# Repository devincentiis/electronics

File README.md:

# My electronic projects shared with every enthusiasts.
## Used KiCAD EDA for design schematic diagrams and PCB 

### [Classic ESR meter](https://github.com/devincentiis/electronics/blob/main/AntonioDeVincentiis_classicESRmeter) 
 Open-Source In-Circuit ESR Meter (ATtiny412)

### [PRESSFLOWino](https://github.com/devincentiis/electronics/blob/main/PRESSFLOWino) 
Multimode, customizable press and flow controller with ATmega328P

### [Water Flush Muse](https://github.com/devincentiis/electronics/blob/main/WaterFlushMuse) 
ATtiny412 water waste tank alarm

## License

MIT License

Copyright (c) 2023 to present - Antonio de Vincentiis

Permission is hereby granted, free of charge, to any person obtaining a copy
of this software and associated documentation files (the "Software"), to deal
in the Software without restriction, including without limitation the rights
to use, copy, modify, merge, publish, distribute, sublicense, and/or sell
copies of the Software, and to permit persons to whom the Software is
furnished to do so, subject to the following conditions:

The above copyright notice and this permission notice shall be included in all
copies or substantial portions of the Software.

THE SOFTWARE IS PROVIDED "AS IS", WITHOUT WARRANTY OF ANY KIND, EXPRESS OR
IMPLIED, INCLUDING BUT NOT LIMITED TO THE WARRANTIES OF MERCHANTABILITY,
FITNESS FOR A PARTICULAR PURPOSE AND NONINFRINGEMENT. IN NO EVENT SHALL THE
AUTHORS OR COPYRIGHT HOLDERS BE LIABLE FOR ANY CLAIM, DAMAGES OR OTHER
LIABILITY, WHETHER IN AN ACTION OF CONTRACT, TORT OR OTHERWISE, ARISING FROM,
OUT OF OR IN CONNECTION WITH THE SOFTWARE OR THE USE OR OTHER DEALINGS IN THE
SOFTWARE.

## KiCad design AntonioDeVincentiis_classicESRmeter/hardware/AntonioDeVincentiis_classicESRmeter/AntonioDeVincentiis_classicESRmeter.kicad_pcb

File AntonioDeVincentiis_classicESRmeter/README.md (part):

# 🛠️ Classic ESR meter
In-Circuit ESR Meter standalone ATtiny412 platform.

---

## 🌍 Language / Lingua
Select your preferred language:
* 🇬🇧 [English Version](#-english-version)
* 🇮🇹 [Versione Italiana](#-versione-italiana)

---

*ESRmeter 85C1 100uA - Case Model T*
## 🇬🇧 English Version

### The innovation:💡
What distinguishes this from the many other circuit solutions found online is the inclusion of a 10 Ω resistor in parallel with the electrolytic capacitor under test. While this prevents ESR measurements beyond a few tens of ohms (which are of no practical use), it offers significant advantages: it creates a resistive voltage divider that eliminates the need for constant-current generators, limits the maximum voltage across the component, allows the capacitor to discharge as quickly as it charges, and provides better protection than the standard pair of anti-parallel diodes.

A complete project [Hardware](./hardware/AntonioDeVincentiis_classicESRmeter/), [Firmware](./firmware/AntonioDeVincentiis_classicESRmeter/), and [Case 3D files](./case/) to build a **high-precision analog ESR Meter** optimized for direct *in-circuit* measurements (without desoldering capacitors). The instrument can resolve variations down to **0.01 Ω** in the critical zone of the scale, extending its logarithmic readout up to **20 Ω**.

The software architecture is developed in C++ for the **ATtiny412** using the Arduino IDE (via the `megaTinyCore` library). It performs deterministic sampling at 100 kHz without requiring external Sample & Hold components, using only signal conditioning/amplification through two common BC850C low-noise transistors.

### 🚀 Key Features
* **Realistic In-Circuit Measurement:** Operates at a low excitation voltage to prevent surrounding semiconductor junctions from turning on during in-circuit testing.
* **Synchronous S&H Sampling (Anti-ESL):** Utilizes the hardware **Event System** integrated into AVR 1-series MCUs to synchronize ADC0 with the 100 kHz square wave timer. By sampling exactly ~3 µs after the cycle start, the instrument isolates the ESR, eliminating parasitic inductive reactance (ESL) spikes.
* **Oversampling and Advanced Filtering:** Executes 64x hardware oversampling combined with a software **EMA (Exponential Moving Average)** filter to guarantee a perfectly stable, vibration-free meter needle.
* **Fixed-Point Logarithmic Scale:** Fast polynomial approximation maps ESR values onto the analog microammeter, ensuring extremely high sub-ohm resolution while expanding readability up to 20 Ω.
* **Smart Power Management (Kill-Switch):** Total shutdown via a Latch MOSFET paired with an auto-power-off feature ensures ~0 mA parasitic current draw in standby.

### ⏳ History

This project was born to solve a well-known issue in electronics troubleshooting: making precise, in-circuit ESR measurements without desoldering components. The initial goal was ambitious yet budget-friendly: creating a tool capable of 0.01 Ω sensitivity without relying on expensive and complex microcontrollers.

The development took a few months and progressed through these key milestones:

* **1. Genesis & Simulation:** The initial concept featured fast operational amplifiers and a precision rectifier. SPICE simulations validated the theory, producing millivolt outputs perfectly readable by a 10-bit ADC (ranging from 0.2 mV for 0.01 Ω up to over 400 mV for 20 Ω).
* **2. The Inductance (ESL) Challenge:** Deeper simulation revealed that inductive reactance caused unwanted voltage spikes on the edges of the 100 kHz square wave. This was solved by replacing the standard rectifier with a delayed *Sample & Hold* approach, bypassing the first 3 µs of spikes to sample only the clean plateau.
* **3. Hardware Simplification & Thermal Compensation:** To lower production costs, the external S&H circuit was replaced by utilizing the MCU's internal ADC, conditioning the signal with just two common BJT transistors. To prevent thermal drift from affecting low-range readings, a compensation diode was added. The firmware checks this at boot, warning the user via a sweeping meter needle if the offset shifts outside the 0.95V - 1.05V tolerance.
* **4. Lab Testing & Real-World Validation:** Once the definitive PCBs arrived, real-world tests exceeded expectations. Pairing the board with custom-made, low-cost Kelvin probes allowed the ADC to resolve variations down to 3.33 mΩ.
* **5. Firmware & Dual-Scale Optimization:** The final challenge was fitting the software into an ultra-cheap 50-cent MCU (ATtiny412). By heavily optimizing timers and ADC registers to sample within 1-2 µs, the firmware takes up just 80% of the memory. It implements an intelligent dual-scale system: Scale 1 (0.01 Ω to 1.00 Ω) for maximum precision, and Scale 2 (1 Ω to 20 Ω) for general readings.

### 📐 Pinout & Connections (ATtiny412)

| Pin | Name | Type | Main Function |
| :---: | :---: | :---: | :--- |
| **1** | VDD | Power | +5V Power Supply |
| **2** | PA6 | Output | ~610 Hz Analog PWM Output (Microammeter Control) |
| **3** | PA7 | Input | ADC0 Analog Input / AIN7 Channel (ESR Sensor) |
| **4** | PA1 | Output | 100 kHz Hardware Square Wave Generation (TCA0) |
| **5** | PA2 | Input | Multi-function Button Input (On/Off/Calibration) / Serial in MODE 1 |
| **6** | PA0 | I/O | UPDI Programming Line |
| **7** | PA3 | Output | Latch MOSFET Control (Power Hold) |
| **8** | GND | Power | Common Circuit Ground |

### 🔧 Configuration and Calibration Guide (FIRMWARE_USAGE_MODE)
The firmware implements a guided calibration sequence managed via the `#define FIRMWARE_USAGE_MODE` macro at the top of the sketch:

#### 🟩 Step 1: MODE 0 - Static Hardware Calibration
Set the macro to `0` and upload the firmware. The 100 kHz carrier is deactivated, and the PWM output to the analog meter is forced to its maximum value (`1023`).
1. Rotate the hardware trimmer **RV2** until you measure exactly **1.000 V** at the `SIGNAL_TO_ADC` test point (BJT sensor bias voltage).
2. Adjust trimmer **RV1** to force the needle of your analog microammeter (e.g., 100µA or 1mA) precisely to the full-scale **0 Ω** mark.

<details>
  <summary>💾 <ins>Click here to view the firmware MODE 0(.hex)</ins></summary>
  <br>

```hex
:1000000019C03FC03EC03DC03CC03BC03AC039C033
:1000100038C037C036C035C034C033C033C031C03B
:1000200030C05FC02EC02DC02CC02BC02AC029C03C
:1000300028C027C011241FBECFEFCDBFDFE3DEBF36
:100040008091400080934000811105C098ED21E02F
:1000500094BF209341008CBB1FE3A0E0BFE3E8EC1A
:10006000F3E002C005900D92A630B107D9F72FE357
:10007000A6E0BFE301C01D92AC31B207E1F76FD03B
:10008000A1C1BECF8F9381E080938D0A8FB78F93EC
:10009000EF93FF93E2E1FFE39F9368948FEF0DC02E
:1000A000E89484819581805D9C4F84839583885EEC
:1000B000934080F0848395838FEF9081981B919378
:1000C00090819F4F919390819F4F919390819F4FEB
:1000D000919336F39F91FF91EF918F918FBF8F9105
:1000E00018951F920F920FB60F9211242F933F93E2
:1000F0008F939F93AF93BF93209110063091110679
:1001000080910D3F811120C08091093F90910A3F5D
:10011000A0910B3FB0910C3F820F931FA11DB11D09
:100120008093093F90930A3FA0930B3FB0930C3FFD
:100130008091063F8F5F8093063F8091063F803419
:100140001CF081E080930D3FBF91AF919F918F9103
:100150003F912F910F900FBE0F901F90189588ED33
:1001600090E084BF90936100E0E0F6E083E5828355
:100170008DE0858380E2838381E080838093020227
:100180008093030A9EEF9093260A9093270A9BE0A0
:100190009093000AE0E8FAE02DEF31E026A737A7B8
:1001A000118290E89283848781E1808378948091A2
:1001B00000148093013F809101148093023F80914D
:1001C000013F9091023F845F9140893C910530F05E
:1001D00088E592E08093013F9093023FF89410925B
:1001E000000A8091003F8F7E8093003F8FE08093D4
:1001F000050A88E0809301048093050480E48093DD
:10020000010480E88093020484E08093170492E064
:100210009093020420E12093A0009093A10081E03C
:100220008093000610920106909302061092030636
:1002300097E0909306068093090680930A06109231
:10024000800A8FEF93E08093AE0A9093AF0A1092EA
:10025000A80A1092A90A1092AA0A1092AB0A88ED75
:1002600084BF2093920A80918E0A81FFFCCF81E7A0
:100270008093800A1092000A8CE08093050A109205
:10028000030A87EC90E08093260A9093270A8CE873
:1002900090E08093280A9093290A84E690E0809366
:1002A0002A0A90932B0A83E08093010A809102022C
:1002B00081608093020210920A0A84E680938A0188
:1002C00081E08093930180930B068093000A7894D9
:1002D0004FEF53E062E02FB7F8948091163F909172
:1002E000173FA091183FB091193F2FBF00910E3FCB
:1002F00010910F3F2091103F3091113F801B910BC7
:10030000A20BB30B84369105A105B10520F32FB7DD
:10031000F8948091163F9091173FA091183FB091AB
:10032000193F2FBF80930E3F90930F3FA093103F34
:10033000B093113F80910D3F882369F28091093F6E
:1003400090910A3FA0910B3FB0910C3FF6E0B5951C
:10035000A79597958795FA95D1F78093073F909346
:10036000083FF8942091033F3091043F8091073F6C
:100370009091083F37FF1CC0880F991F880F991F65
:100380008093033F9093043F4093AA0A5093AB0A93
:100390006093840A1092093F10920A3F10920B3F1B
:1003A00010920C3F1092063F10920D3F789493CF1D
:1003B000F901F595E795F595E7958E1B9F0B820F53
:0803C000931FDECFF894FFCF7C
:0603C800FF5802FFFF00D8
:00000001FF
```

</details>

#### 🟦 Step 2: MODE 1 - Debug and Constant Acquisition
Set the macro to `1` and upload the firmware. This mode activates the 100 kHz signal and enables a software serial port on pin `PA2` at 9600 baud.
1. Connect a USB-TTL converter (Converter Rx to MCU pin PA2).
2. Open the Serial Monitor and note the `ADC_RAW` value with shorted probes (`ADC_ZERO`, typically ~945) and open probes (`ADC_OPEN`, typically ~130).
3. If your real-world values differ from the default ones, update the definitions at the top of the sketch before the final flash.

<details>
  <summary>💾 <ins>Click here to view the firmware MODE 1(.hex)</ins></summary>
  <br>

```hex
:100000001BC04BC04AC01CC248C047C046C045C008
:1000100044C043C042C041C040C03FC0E2C13DC037
:100020003CC058C23AC039C038C037C036C035C0ED
:1000300034C033C02405960511241FBECFEFCDBFB9
:10004000DFE3DEBF8091400080934000811105C056
:1000500098ED21E094BF209341008CBB1FE3A0E00A
:10006000BFE3E2EFFCE002C005900D92A830B107BB
:10007000D9F72FE3A8E0BFE301C01D92AD38B20766
:10008000E1F710E0CBE1D0E003C02197FE01DBD522
:10009000CA31D107D1F75CD2E8C5B2CFE0915A3F5F
:1000A000F0915B3F309709F44DC0A285B3858185FF
:1000B000928D91FF04C09C91892329F408959C910D
:1000C000892309F03FC0A785B0899C9181898095DB
:1000D00089238C93828993890197F1F764897589C3
:1000E000A285B385518538E020E0CB010197F1F777
:1000F000822F90E095958795282F4C91452309F004
:100100002068315091F7828D81FD20958091593F73
:1001100090E001968F7399273091583F381799F0E6
:10012000A091593FB0E0A85EB04C2C938093593F0A
:10013000868997890197F1F7A785B0898C91918974
:10014000892B8C930895828D8160828FF1CFAF923D
:10015000BF92CF92DF92EF92FF920F931F93CF93B4
:10016000DF936C017B018B01040F151FEB015E0116
:10017000AE18BF08C017D10759F06991D601ED91AB
:10018000FC910190F081E02DC6010995892B79F74A
:10019000C501DF91CF911F910F91FF90EF90DF90FC
:1001A000CF90BF90AF90089520915A3F30915B3F20
:1001B0002817390771F49091583F8091593F98174B
:1001C00041F0E091583FF0E0E85EF04C808190E033
:1001D00008958FEF9FEF08950895EF92FF920F9388
:1001E0001F93CF93DF93DC015896ED90FC905997C5
:1001F000E114F10479F481E090E012968D939C93E0
:10020000139790E080E0DF91CF911F910F91FF90C5
:10021000EF9008951D96ED91FC911E971C968C9180
:100220001C97982F90950FB75A962C915A97122F8A
:10023000127021FD6095F8942081112319F1282B6B
:100240002083E7012197F1F728E0462F50E0308125
:1002500060FF1AC0382B3083E7012197F1F7BA010C
:1002600075956795215089F7112381F08081892345
:1002700080830FBF58968D919C910197F1F781E093
:1002800090E0C1CF2923DCCF3923E5CF9081892BA2
:10029000EFCF20915A3F30915B3F2817390741F447
:1002A0008091593F9091583F891B8F7390E008953A
:1002B00090E080E0089520915A3F30915B3F2817ED
:1002C0003907A1F49091583F8091593F981771F0E8
:1002D000E091583FF0E0E85EF04C80819091583F0B
:1002E0009F5F9F739093583F90E008958FEF9FEF2B
:1002F000089590E080E00895FC0101900020E9F766
:100300003197AF01481B590BBC0182E79FE31FCF18
:100310008F929F92AF92BF920F931F93CF93DF93D1
:10032000CDB7DEB7A197CDBFDEBF19A2423008F42A
:100330004AE08E010F5D1F4F842E912CB12CA12C11
:10034000A501940132D4E62FB901CA01EA30D4F4F0
:10035000E05DD801EE938D01232B242B252B81F713
:1003600090E080E0109711F0CD01C6DFA196CDBFDF
:10037000DEBFDF91CF911F910F91BF90AF909F9003
:100380008F900895E95CE5CFCF92DF92EF92FF92D4
:10039000CF93DF936C01990FEE08FF08F7FE17C0AB
:1003A0006DE282E79FE319DFEC0166277727CB0137
:1003B0006C197D098E099F094AE0AADF8C0F9D1FE9
:1003C000DF91CF91FF90EF90DF90CF9008954AE0BA
:1003D000C701B601DF91CF91FF90EF90DF90CF90F2
:1003E00097CF8F9381E080938D0A8FB78F93EF9390
:1003F000FF93E8E6FFE39F9368948FEF0DC0E894C6
:1004000084819581805D9C4F84839583885E934031
:1004100080F0848395838FEF9081981B91939081D6
:100420009F4F919390819F4F919390819F4F919374
:1004300036F39F91FF91EF918F918FBF8F91189518
:100440000F9300E000C00F920FB60F921F9211247D
:10045000FF921F932F933F934F935F936F937F93DD
:100460008F939F93AF93BF93CF93DF93EF93FF93BC
:10047000A1E0BFE3A00FB11DCD91DC91000F0D5F96
:10048000A02FB0E0FC90109761F01F2D169518F08A
:1004900041F02296FBCFE991F9913097B9F3099594
:1004A000F5CFA02FB0E0FC92FF91EF91DF91CF91BB
:1004B000BF91AF919F918F917F916F915F914F917C
:1004C0003F912F911F91FF901F900F900FBE0F90A3
:1004D0000F9118951F920F920FB60F9211242F9320
:1004E0003F938F939F93AF93BF93209110063091CA
:1004F00011068091633F811120C080915F3F9091F0
:10050000603FA091613FB091623F820F931FA11D98
:10051000B11D80935F3F9093603FA093613FB09384
:10052000623F80915C3F8F5F80935C3F80915C3F36
:1005300080341CF081E08093633FBF91AF919F9125
:100540008F913F912F910F900FBE0F901F90189594
:1005500088ED90E084BF90936100E0E0F6E083E5F1
:1005600082838DE0858380E2838381E08083809332
:1005700002028093030A9EEF9093260A9093270A23
:100580009BE09093000AE0E8FAE02DEF31E026A727
:1005900037A7118290E89283848781E180837894E1
:1005A000809100148093033F809101148093043F55
:1005B0008091033F9091043F845F9140893C910575
:1005C00030F088E592E08093033F9093043FF894E5
:1005D0001092000A8091003F8F7E8093003F8FE051
:1005E0008093050A88E0809301048093050480E4E9
:1005F0008093010480E88093020484E080931704D0
:1006000092E09093010420E12093A0009093A10038
:1006100081E08093000610920106909302061092EA
:10062000030697E0909306068093090680930A06D6
:100630001092800A8FEF93E08093AE0A9093AF0AF6
:100640001092A80A1092A90A1092AA0A1092AB0A54
:1006500088ED84BF2093920A80918E0A81FFFCCF9F
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
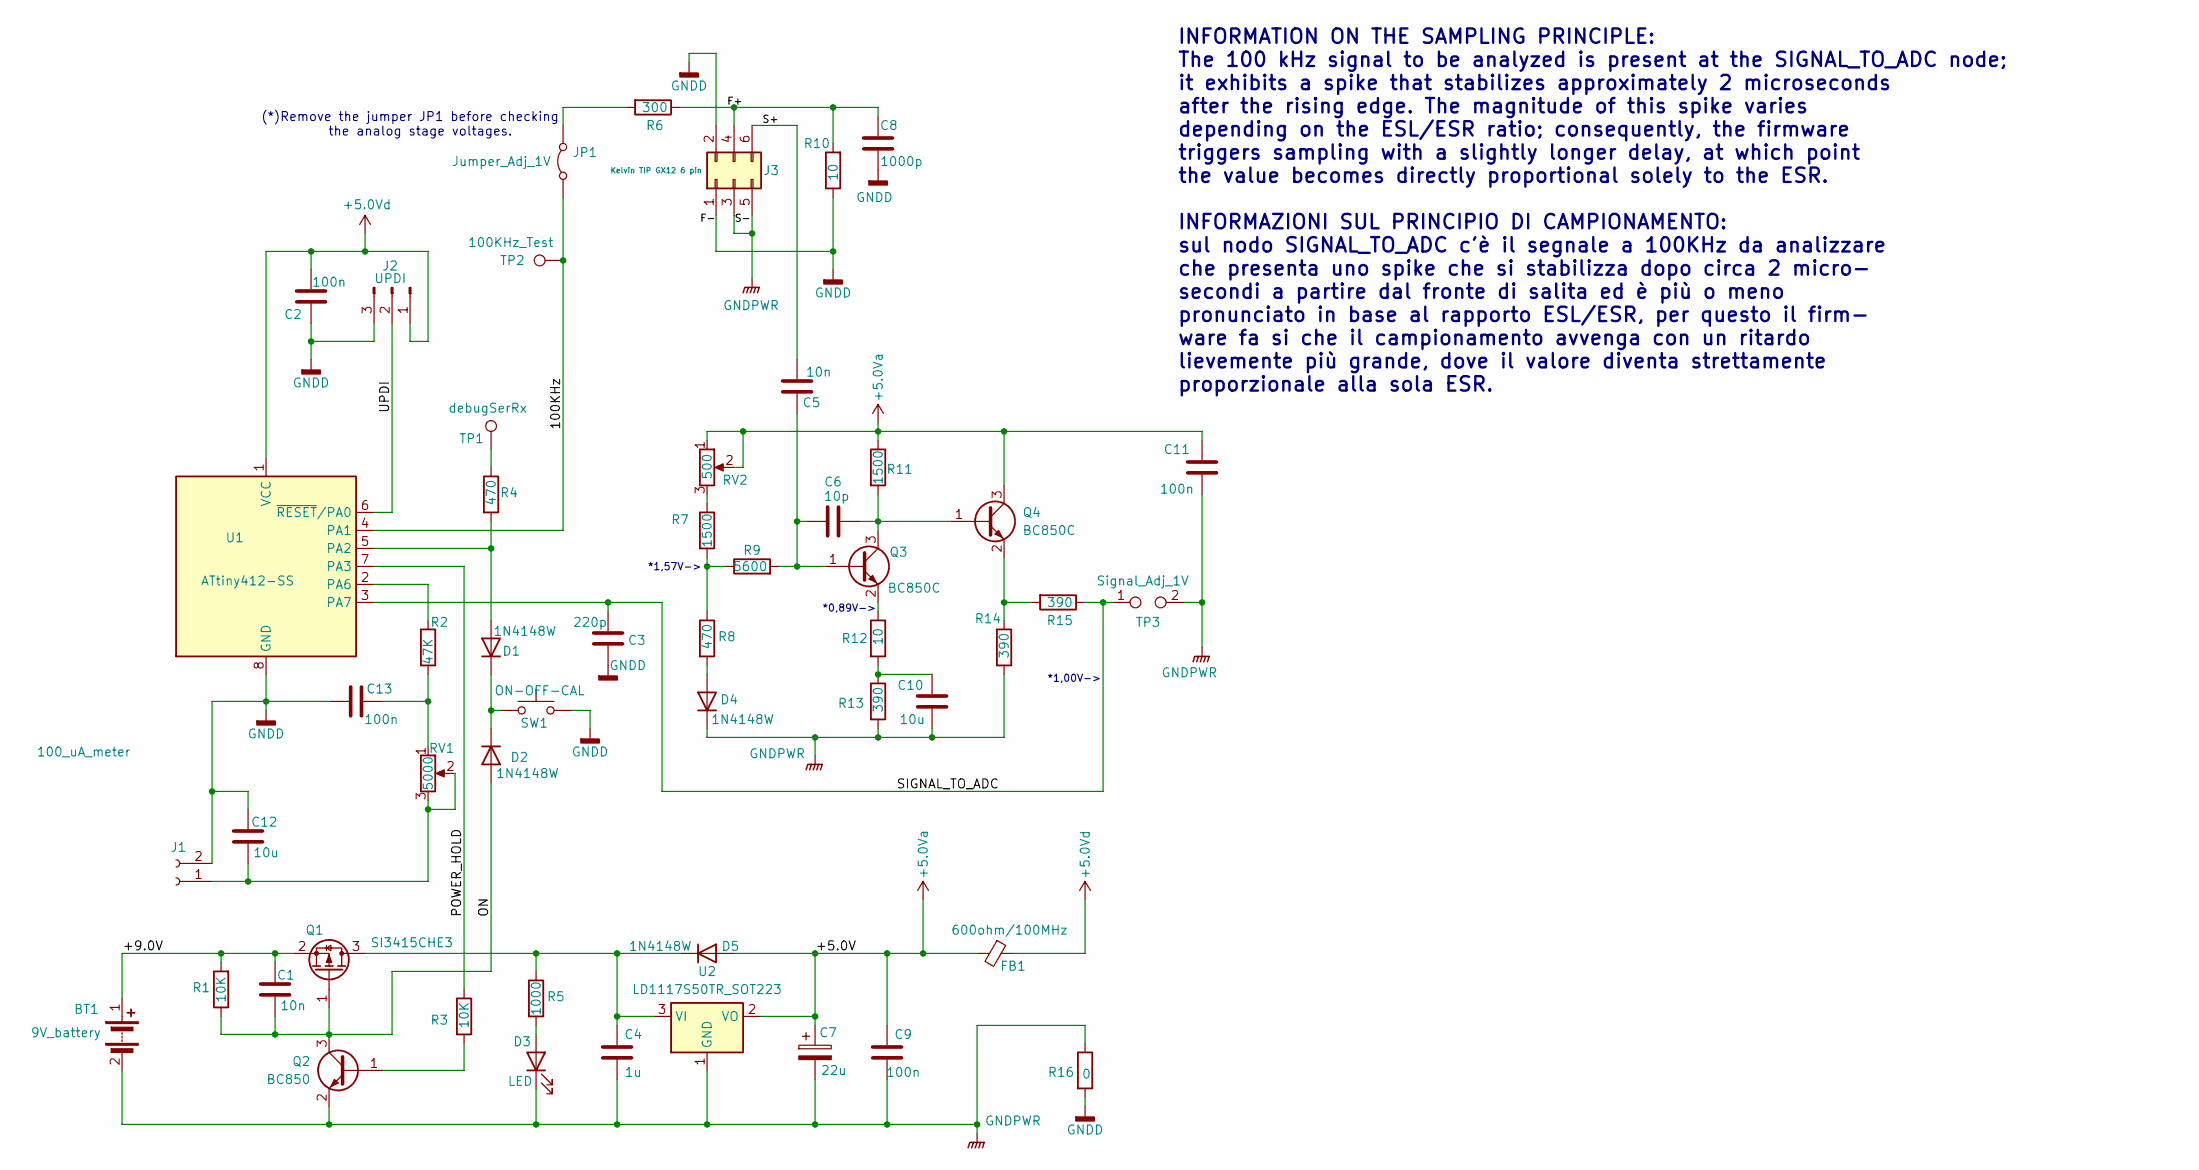
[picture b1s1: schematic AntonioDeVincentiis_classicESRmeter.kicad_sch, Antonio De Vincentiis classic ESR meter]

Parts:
BT1: 9V_battery; PinSocket_1x02_P2.54mm_Vertical
C1, C5: 10n; C_0805_2012Metric_Pad1.18x1.45mm_HandSolder
C2, C9, C11, C13: 100n; C_0805_2012Metric_Pad1.18x1.45mm_HandSolder
C3: 220p; C_0805_2012Metric_Pad1.18x1.45mm_HandSolder
C4: 1u; C_0805_2012Metric_Pad1.18x1.45mm_HandSolder
C6: 10p; C_0805_2012Metric_Pad1.18x1.45mm_HandSolder
C7: 22u; CP_Elec_5x5.9
C8: 1000p; C_0805_2012Metric_Pad1.18x1.45mm_HandSolder
C10, C12: 10u; C_0805_2012Metric_Pad1.18x1.45mm_HandSolder
D1, D2, D4, D5: 1N4148W; D_SOD-123
D3: LED; LED_D3.0mm_Clear
FB1: 600ohm/100MHz; L_0805_2012Metric_Pad1.05x1.20mm_HandSolder
J1: 100_uA_meter; PinSocket_1x02_P2.54mm_Vertical
J2: UPDI; PinSocket_1x03_P2.54mm_Vertical
J3: Kelvin TIP GX12 6 pin; PinSocket_2x03_P2.54mm_Vertical
JP1: Jumper_Adj_1V; PinHeader_2x01_P2.54mm_Vertical
Q1: SI3415CHE3; SOT-23_Handsoldering
Q2: BC850; SOT-23
Q3, Q4: BC850C; SOT-23
R1, R3: 10K; R_0805_2012Metric_Pad1.20x1.40mm_HandSolder
R2: 47K; R_0805_2012Metric_Pad1.20x1.40mm_HandSolder
R4, R8: 470; R_0805_2012Metric_Pad1.20x1.40mm_HandSolder
R5: 1000; R_0805_2012Metric_Pad1.20x1.40mm_HandSolder
R6: 300; R_0805_2012Metric_Pad1.20x1.40mm_HandSolder
R7, R11: 1500; R_0805_2012Metric_Pad1.20x1.40mm_HandSolder
R9: 5600; R_0805_2012Metric_Pad1.20x1.40mm_HandSolder
R10: 10; R_2010_5025Metric_Pad1.40x2.65mm_HandSolder
R12: 10; R_0805_2012Metric_Pad1.20x1.40mm_HandSolder
R13, R14, R15: 390; R_0805_2012Metric_Pad1.20x1.40mm_HandSolder
R16: 0; R_0805_2012Metric_Pad1.20x1.40mm_HandSolder
RV1: 5000; Potentiometer_Bourns_3296W_Vertical
RV2: 500; Potentiometer_Bourns_3296W_Vertical
SW1: ON-OFF-CAL; SW_PUSH_6mm_H5mm
TP1: debugSerRx; PinSocket_1x01_P2.54mm_Vertical
TP2: 100KHz_Test; PinSocket_1x01_P2.54mm_Vertical
TP3: Signal_Adj_1V; PinSocket_1x02_P2.54mm_Vertical
U1: ATtiny412-SS; SOIC-8_3.9x4.9mm_P1.27mm
U2: LD1117S50TR_SOT223; SOT-223-3_TabPin2

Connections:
+5.0Va: C7.1, C9.1, C11.1, D5.2 (A), FB1.2, Q4.3 (C), R11.1, RV2.1, RV2.2, U2.2 (VO)
+5.0Vd: C2.1, FB1.1, J2.1, U1.1 (VCC)
/100KHz: JP1.1 (A), TP2.1 (1_1), U1.4 (PA1)
/+9.0V: BT1.1 (+4.5V), C1.1, Q1.2 (S), R1.2
/F+: C8.1, J3.4, R6.1, R10.2
/ON: C1.2, D2.2 (A), Q1.1 (G), Q2.3 (C), R1.1
/POWER_HOLD: R3.1, U1.7 (PA3)
/S+: C5.1, J3.6
/SIGNAL_TO_ADC: C3.1, R15.1, TP3.1, U1.3 (PA7)
/UPDI: J2.2, U1.6 (~RESET/PA0)
GNDD: C2.2, C3.2, C8.2, C12.1, C13.1, J1.2, J2.3, J3.1, J3.2, R10.1, R16.2, SW1.2, U1.8 (GND)
GNDPWR: BT1.2 (-), C4.2, C7.2, C9.2, C10.2, C11.2, D3.1 (K), D4.1 (K), J3.3, J3.5, Q2.2 (E), R13.2, R14.2, R16.1, TP3.2, U2.1 (GND)
unnamed: C10.1, R12.2, R13.1
unnamed: C13.2, R2.2, RV1.1
unnamed: D1.2 (A), R4.2, U1.5 (PA2)
unnamed: D1.1 (K), D2.1 (K), SW1.1
unnamed: D3.2 (A), R5.2
unnamed: D4.2 (A), R8.2
unnamed: C4.1, D5.1 (K), Q1.3 (D), R5.1, U2.3 (VI)
unnamed: C12.2, J1.1, RV1.2, RV1.3
unnamed: JP1.2 (B), R6.2
unnamed: Q2.1 (B), R3.2
unnamed: C5.2, C6.1, Q3.1 (B), R9.2
unnamed: C6.2, Q3.3 (C), Q4.1 (B), R11.2
unnamed: Q3.2 (E), R12.1
unnamed: Q4.2 (E), R14.1, R15.2
unnamed: R4.1, TP1.1 (1_1)
unnamed: R7.1, RV2.3
unnamed: R7.2, R8.1, R9.1
unnamed: R2.1, U1.2 (PA6)

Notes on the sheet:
*1,00V->
*0,89V->
*1,57V->
INFORMATION ON THE SAMPLING PRINCIPLE: The 100 kHz signal to be analyzed is present at the SIGNAL_TO_ADC node; it exhibits a spike that stabilizes approximately 2 microseconds after the rising edge. The magnitude of this spike varies depending on the ESL/ESR ratio; consequently, the firmware trigge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
(*)Remove the jumper JP1 before checking the analog stage voltages.

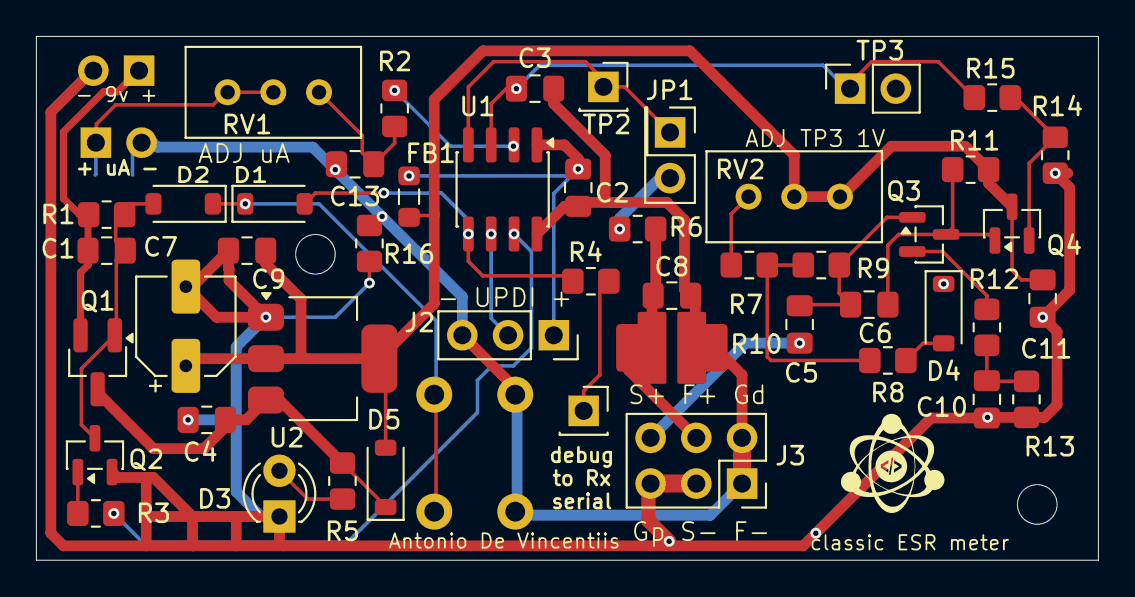
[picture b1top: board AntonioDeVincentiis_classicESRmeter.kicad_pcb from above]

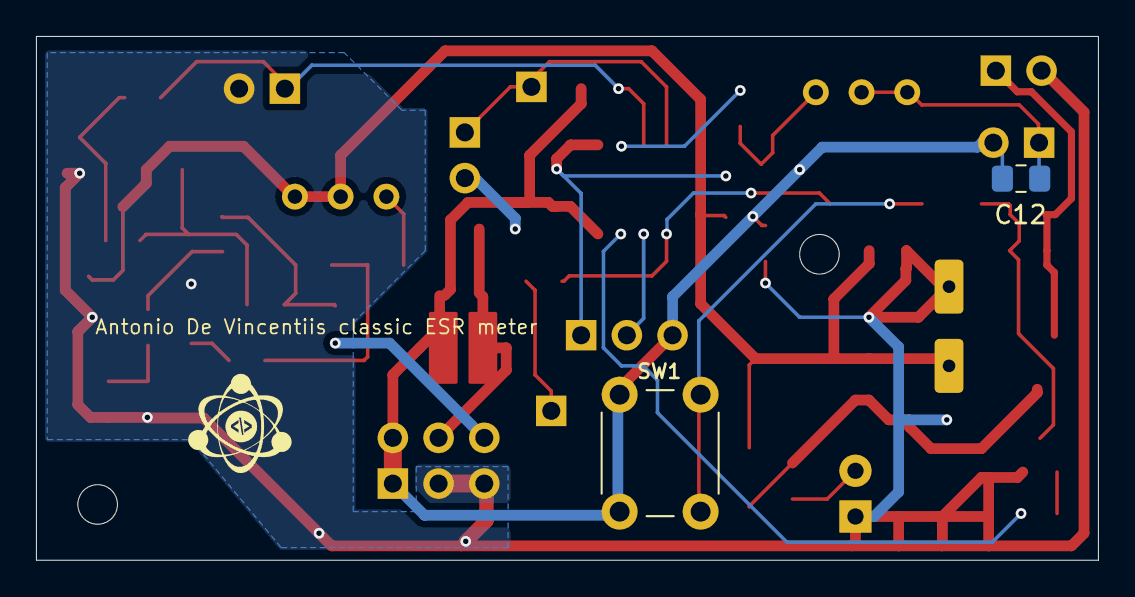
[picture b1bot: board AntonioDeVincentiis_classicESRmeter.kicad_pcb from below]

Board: 2 copper layers, 59.0 x 29.1 mm, 52 parts (2 on the bottom side), 30 nets.

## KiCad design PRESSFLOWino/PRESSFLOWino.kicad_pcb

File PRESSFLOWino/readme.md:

# PRESSFLOWino - Multimode, customizable press and flow controller
## for air compressor, water pump and other device

Base on Atmel ATmega328P 32 pins and compiled trought Arduino IDE and ADVcapacitiveSensor library. The circuit is shared for the purpose of making you participate in the improvement of the [FIRMWARE](https://github.com/devincentiis/electronics/blob/main/PRESSFLOWino/firmwarePressFlow/firmwarePressFlow.ino); for safety reasons and $\textsf{\color{orange}{to avoid risks of electric shock it is essential to power it at 48 Vac}}$ for the Triacs and at 5 Vdc for the digital section. Therefore, **anyone attempting to implement it in practice must be qualified and assumes all civil and criminal liability.**

**DECLARATION OF RESPONSIBILITY**

**The author therefore assumes NO RESPONSIBILITY** in civil or criminal matters and does not offer any implicit or explicit guarantee, and is not responsible for problems of any kind, damages or accidents deriving from the use of the information found on this web page , as well as from the use of the page itself or part of it. **Anyone who creates and/or uses modifications, diagrams, electrical circuits**, or mechanical parts or electronic theory information described here, **does so as their own free choice, assuming all responsibilities that may derive from them**, and will therefore not be able to claim any form of compensation from the author, in case of damage or accidents for everything described and said. In light of the above and **in consideration of the danger of electrocution deriving from the connection with voltages highter than 48V ac**, the description on this project has been deliberately omitted and **remains the responsibility of qualified personnel in the electrical/electronic sector**.

### Use instructions
By touch the 4 buttons (ENTER, UP, DOWN, BACK) you can select the parameters for the target device of the control.
* Select the type of device to control: pump or compressor.
* Select the pressure sensor or customize it.
* Select flow sensor as switch, none, preset or customize it.

### Schematic and PCB EDA [KiCad](https://www.kicad.org/download/) 

### Firmware library for [Arduino IDE](https://github.com/arduino/Arduino) 

| Reference        | Value        | Footprint                                                      | Qty |
|------------------|--------------|----------------------------------------------------------------|-----|
| BZ1              | Buzzer       | Buzzer_Beeper:Buzzer_12x9.5RM7.6                               | 1   |
| C1,C6,C7,C10,C13 | 100n         | Capacitor_SMD:C_1206_3216Metric_Pad1.33x1.80mm_HandSolder      | 5   |
| C2,C4            | 100n 400V    | Capacitor_THT:C_Rect_L19.0mm_W6.0mm_P15.00mm_MKS4              | 2   |
| C3               | 10n 400V     | Capacitor_THT:C_Rect_L13.0mm_W5.0mm_P10.00mm_FKS3_FKP3_MKS4    | 1   |
| C5               | 470u         | Capacitor_THT:CP_Radial_D12.5mm_P5.00mm                        | 1   |
| C8               | 10u          | Capacitor_THT:CP_Radial_D5.0mm_P2.50mm                         | 1   |
| C9               | 10nF         | Capacitor_THT:C_Rect_L13.0mm_W5.0mm_P10.00mm_FKS3_FKP3_MKS4    | 1   |
| D1               | LED-ORANGE   | LED_SMD:LED_1206_3216Metric_Pad1.42x1.75mm_HandSolder          | 1   |
| D2,D7            | BT137-600    | Package_TO_SOT_THT:TO-220-3_Vertical                           | 2   |
| D4               | LED-GREEN    | LED_SMD:LED_1206_3216Metric_Pad1.42x1.75mm_HandSolder          | 1   |
| D5,D8            | M4-1N4004    | Diode_SMD:D_SMA                                                | 2   |
| DS1              | 16x02        | Display:WC1602A                                                | 1   |
| F1               | FUSE         | Fuse_THT:Rect_L7.2mm_W4.5mm_P5.00mm                            | 1   |
| H1               | BCK          | MountingHole:MountingHole_3.2mm_M3_Pad_TopBottom               | 1   |
| H2               | ENT          | MountingHole:MountingHole_3.2mm_M3_Pad_TopBottom               | 1   |
| H3               | UP           | MountingHole:MountingHole_3.2mm_M3_Pad_TopBottom               | 1   |
| H4               | DWN          | MountingHole:MountingHole_3.2mm_M3_Pad_TopBottom               | 1   |
| IC1,IC2          | TLP266J      | Package_SO:SO-4_4.4x4.3mm_P2.54mm                              | 2   |
| J1               | ICSP         | Connector_PinHeader_2.54mm:PinHeader_2x03_P2.54mm_Vertical     | 1   |
| J2               | FTDI         | Connector_PinSocket_2.54mm:PinSocket_1x06_P2.54mm_Vertical     | 1   |
| P1               | E_VALVE      | ADVlibrary:Faston6.35-2x7.62                                   | 1   |
| P2               | V ac         | ADVlibrary:Faston6.35-2x7.62                                   | 1   |
| P3               | MOTOR        | ADVlibrary:Faston6.35-2x7.62                                   | 1   |
| P4               | GROUND       | ADVlibrary:Faston6.35-2x7.62                                   | 1   |
| R1,R2,R3,R4      | 4.7M         | Resistor_SMD:R_1206_3216Metric_Pad1.30x1.75mm_HandSolder       | 4   |
| R5,R6,R7,R8,R19  | 1000         | Resistor_SMD:R_1206_3216Metric_Pad1.30x1.75mm_HandSolder       | 5   |
| R9               | 470          | Resistor_SMD:R_1206_3216Metric_Pad1.30x1.75mm_HandSolder       | 1   |
| R10,R16          | 330          | Resistor_SMD:R_2512_6332Metric_Pad1.40x3.35mm_HandSolder       | 2   |
| R11,R17          | 390          | Resistor_SMD:R_2512_6332Metric_Pad1.40x3.35mm_HandSolder       | 2   |
| R12,R18          | 39           | Resistor_SMD:R_2512_6332Metric_Pad1.40x3.35mm_HandSolder       | 2   |
| R14,R15          | 120          | Resistor_SMD:R_1206_3216Metric_Pad1.30x1.75mm_HandSolder       | 2   |
| R20              | 10K          | Resistor_SMD:R_1206_3216Metric_Pad1.30x1.75mm_HandSolder       | 1   |
| R21              | 20K          | Resistor_SMD:R_1206_3216Metric_Pad1.30x1.75mm_HandSolder       | 1   |
| RV1              | 5K           | Potentiometer_THT:Potentiometer_Bourns_3266Y_Vertical          | 1   |
| U1               | ATmega328P   | Package_QFP:TQFP-32_7x7mm_P0.8mm                               | 1   |
| U2               | FLOW_SENS    | Connector_PinSocket_2.54mm:PinSocket_1x03_P2.54mm_Vertical     | 1   |
| U3               | PRESS_SENS   | Connector_PinSocket_2.54mm:PinSocket_1x03_P2.54mm_Vertical     | 1   |
| U4               | L7805        | Package_TO_SOT_SMD:SOT-89-3                                    | 1   |

### Assembling

## License

MIT License

Copyright (c) 2025 to present - Antonio de Vincentiis

Permission is hereby granted, free of charge, to any person obtaining a copy
of this software and associated documentation files (the "Software"), to deal
in the Software without restriction, including without limitation the rights
to use, copy, modify, merge, publish, distribute, sublicense, and/or sell
copies of the Software, and to permit persons to whom the Software is
furnished to do so, subject to the following conditions:

The above copyright notice and this permission notice shall be included in all
copies or substantial portions of the Software.

THE SOFTWARE IS PROVIDED "AS IS", WITHOUT WARRANTY OF ANY KIND, EXPRESS OR
IMPLIED, INCLUDING BUT NOT LIMITED TO THE WARRANTIES OF MERCHANTABILITY,
FITNESS FOR A PARTICULAR PURPOSE AND NONINFRINGEMENT. IN NO EVENT SHALL THE
AUTHORS OR COPYRIGHT HOLDERS BE LIABLE FOR ANY CLAIM, DAMAGES OR OTHER
LIABILITY, WHETHER IN AN ACTION OF CONTRACT, TORT OR OTHERWISE, ARISING FROM,
OUT OF OR IN CONNECTION WITH THE SOFTWARE OR THE USE OR OTHER DEALINGS IN THE
SOFTWARE.

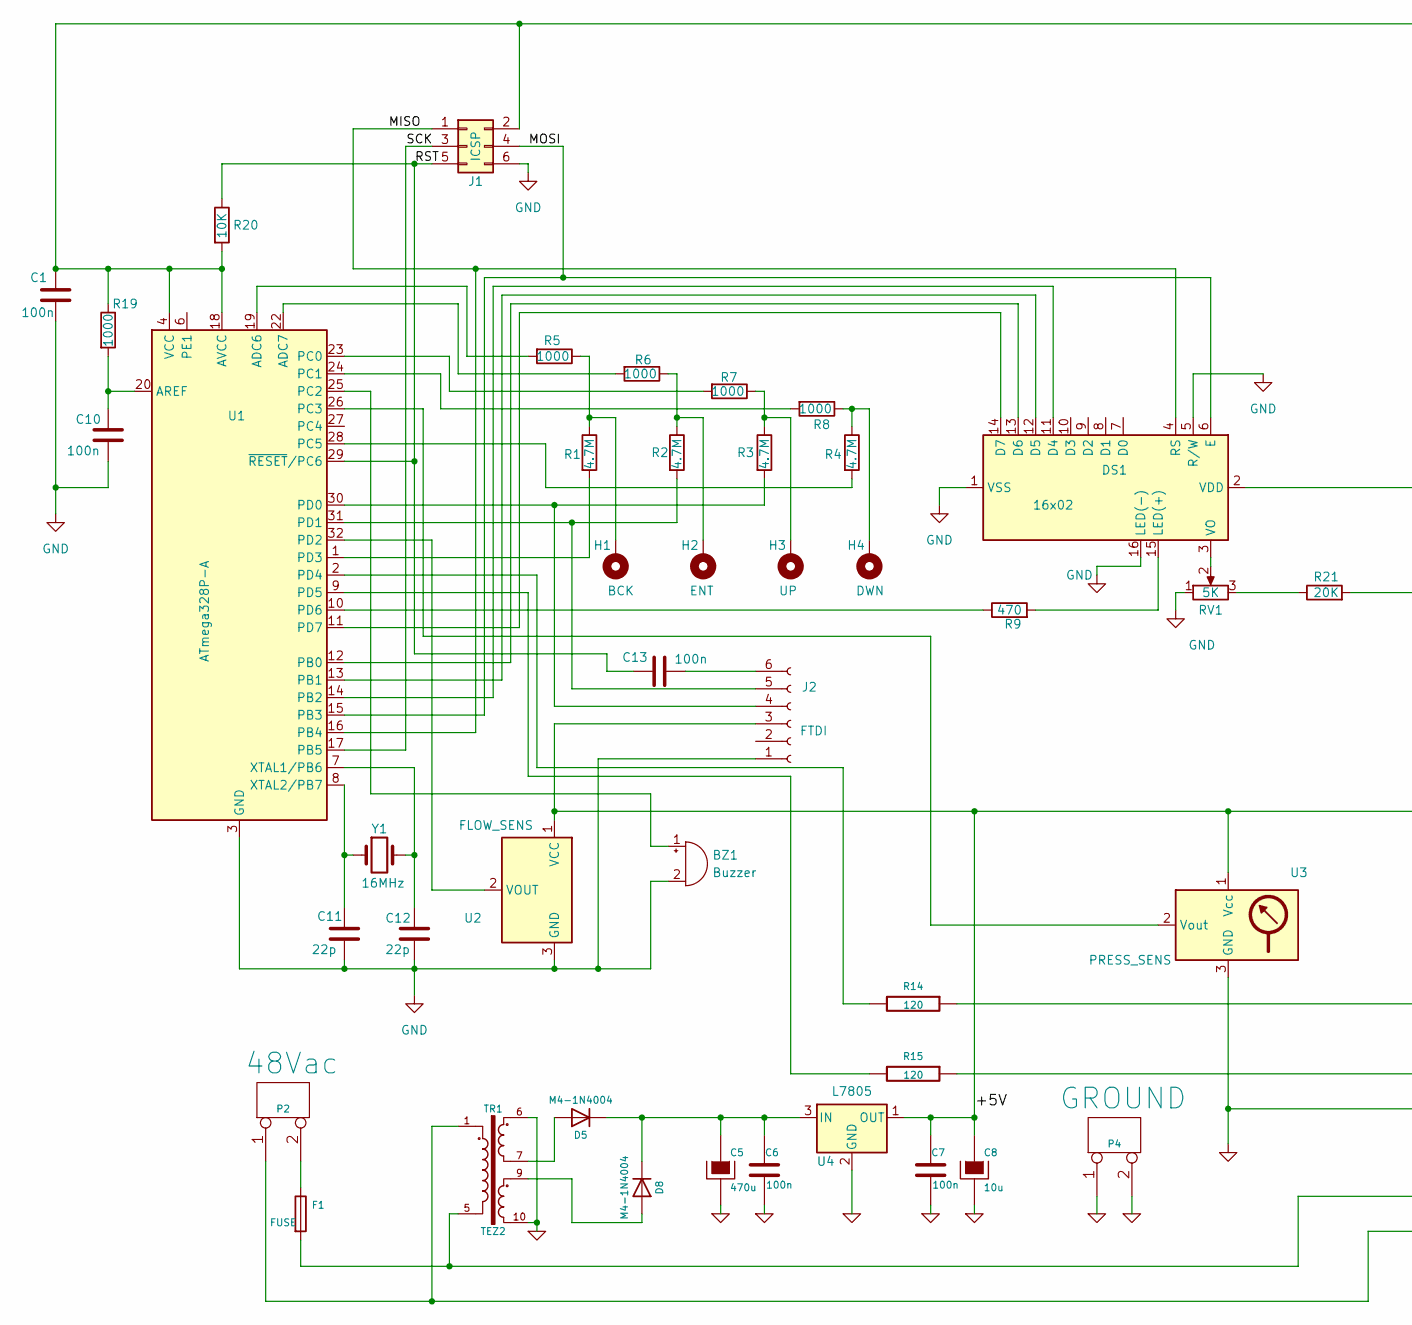
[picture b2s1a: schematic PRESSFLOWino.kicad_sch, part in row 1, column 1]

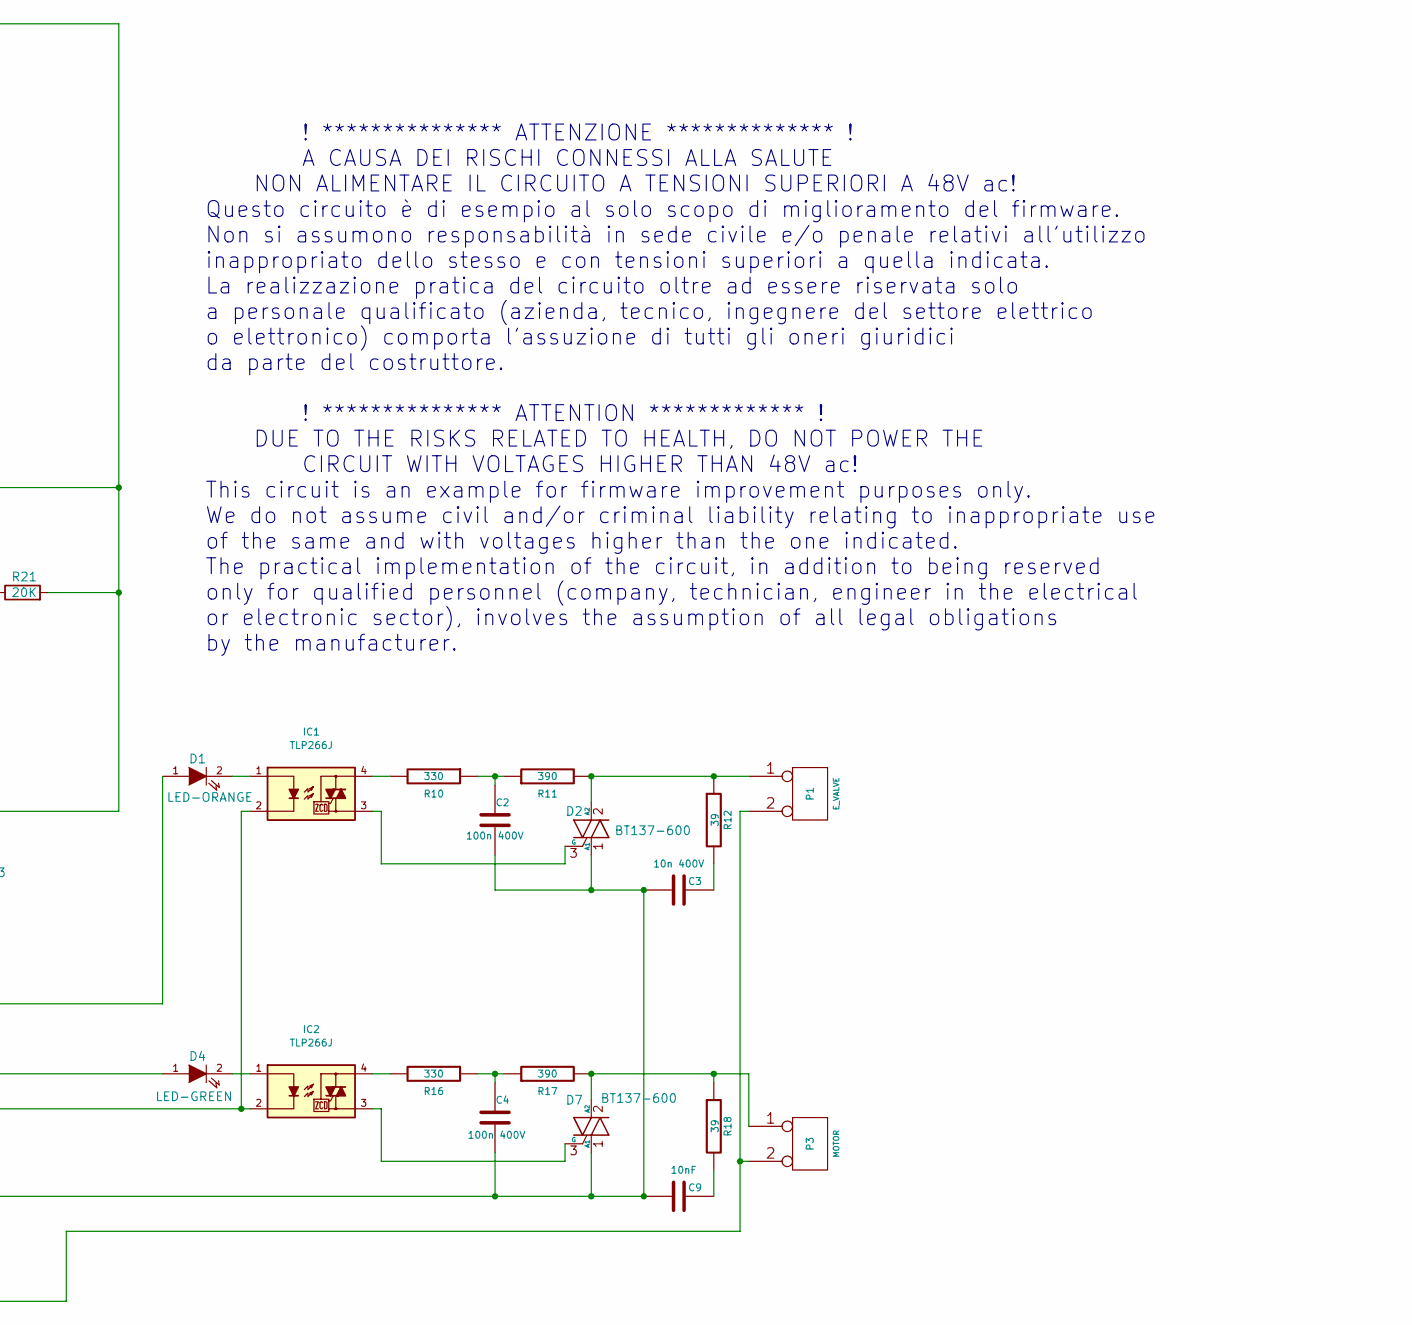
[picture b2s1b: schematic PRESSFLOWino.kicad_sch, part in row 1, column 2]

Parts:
BZ1: Buzzer; Buzzer_12x9.5RM7.6
C1, C6, C7, C10, C13: 100n; C_1206_3216Metric_Pad1.33x1.80mm_HandSolder
C2, C4: 100n 400V; C_Rect_L19.0mm_W6.0mm_P15.00mm_MKS4
C3: 10n 400V; C_Rect_L13.0mm_W5.0mm_P10.00mm_FKS3_FKP3_MKS4
C5: 470u; CP_Radial_D12.5mm_P5.00mm
C8: 10u; CP_Radial_D5.0mm_P2.50mm
C9: 10nF; C_Rect_L13.0mm_W5.0mm_P10.00mm_FKS3_FKP3_MKS4
C11, C12: 22p; C_1206_3216Metric_Pad1.33x1.80mm_HandSolder
D1: LED-ORANGE; LED_1206_3216Metric_Pad1.42x1.75mm_HandSolder
D2, D7: BT137-600; TO-220-3_Vertical
D4: LED-GREEN; LED_1206_3216Metric_Pad1.42x1.75mm_HandSolder
D5, D8: M4-1N4004; D_SMA
DS1: 16x02; WC1602A
F1: FUSE; C_Rect_L7.2mm_W4.5mm_P5.00mm_FKS2_FKP2_MKS2_MKP2
H1: BCK; MountingHole_3.2mm_M3_Pad_TopBottom
H2: ENT; MountingHole_3.2mm_M3_Pad_TopBottom
H3: UP; MountingHole_3.2mm_M3_Pad_TopBottom
H4: DWN; MountingHole_3.2mm_M3_Pad_TopBottom
IC1, IC2: TLP266J; SO-4_4.4x4.3mm_P2.54mm
J1: ICSP; PinHeader_2x03_P2.54mm_Vertical
J2: FTDI; PinSocket_1x06_P2.54mm_Vertical
P1: E_VALVE; Faston6.35-2x7.62
P2: 48Vac; Faston6.35-2x7.62
P3: MOTOR; Faston6.35-2x7.62
P4: GROUND; Faston6.35-2x7.62
R1, R2, R3, R4: 4.7M; R_1206_3216Metric_Pad1.30x1.75mm_HandSolder
R5, R6, R7, R8, R19: 1000; R_1206_3216Metric_Pad1.30x1.75mm_HandSolder
R9: 470; R_1206_3216Metric_Pad1.30x1.75mm_HandSolder
R10, R16: 330; R_2512_6332Metric_Pad1.40x3.35mm_HandSolder
R11, R17: 390; R_2512_6332Metric_Pad1.40x3.35mm_HandSolder
R12, R18: 39; R_2512_6332Metric_Pad1.40x3.35mm_HandSolder
R14, R15: 120; R_1206_3216Metric_Pad1.30x1.75mm_HandSolder
R20: 10K; R_1206_3216Metric_Pad1.30x1.75mm_HandSolder
R21: 20K; R_1206_3216Metric_Pad1.30x1.75mm_HandSolder
RV1: 5K; Potentiometer_Bourns_3266Y_Vertical
TR1: TEZ2; Transformer_Breve_TEZ-28x33
U1: ATmega328P-A; TQFP-32_7x7mm_P0.8mm
U2: FLOW_SENS; PinSocket_1x03_P2.54mm_Vertical
U3: PRESS_SENS; PinSocket_1x03_P2.54mm_Vertical
U4: L7805; SOT-89-3
Y1: 16MHz; Crystal_HC52-6mm_Vertical

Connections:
/+5V: C1.1, C7.1, C8.1, DS1.2 (VDD), J1.2, J2.3, R19.1, R20.2, R21.2, U1.4 (VCC), U1.18 (AVCC), U2.1 (VCC), U3.1 (Vcc), U4.1 (OUT)
/MISO: DS1.4 (RS), J1.1, U1.16 (PB4)
/MOSI: DS1.6 (E), J1.4, U1.15 (PB3)
/RST: C13.1, J1.5, R20.1, U1.29 (~RESET/PC6)
/SCK: J1.3, U1.17 (PB5)
GND: BZ1.2 (-), C1.2, C5.2, C6.2, C7.2, C8.2, C10.2, C11.2, C12.2, DS1.1 (VSS), DS1.5 (R/W), DS1.16 (LED(-)), IC1.2, IC2.2, J1.6, J2.1, P4.1, P4.2 (PM), RV1.1, TR1.6, TR1.10, U1.3 (GND), U1.5 (GND), U1.21 (GND), U2.3 (GND), U3.3 (GND), U4.2 (GND)
unnamed: BZ1.1 (+), U1.25 (PC2)
unnamed: C2.1, R10.1, R11.1
unnamed: C3.1, R12.2
unnamed: C4.1, R16.1, R17.1
unnamed: C9.1, R18.2
unnamed: D1.1 (A), R14.1
unnamed: D1.2 (K), IC1.1
unnamed: C2.2, C3.2, C4.2, C9.2, D2.1 (A1), D7.1 (A1), F1.2, TR1.5
unnamed: D2.2 (A2), P1.1, R11.2, R12.1
unnamed: D2.3 (G), IC1.3
unnamed: D4.1 (A), R15.1
unnamed: D4.2 (K), IC2.1
unnamed: D5.2 (A), TR1.7
unnamed: C5.1, C6.1, D5.1 (K), D8.1 (K), U4.3 (IN)
unnamed: D7.2 (A2), P3.1, R17.2, R18.1
unnamed: D7.3 (G), IC2.3
unnamed: D8.2 (A), TR1.9
unnamed: DS1.11 (D4), U1.14 (PB2)
unnamed: DS1.12 (D5), U1.13 (PB1)
unnamed: DS1.13 (D6), U1.12 (PB0)
unnamed: DS1.14 (D7), U1.11 (PD7)
unnamed: DS1.15 (LED(+)), R9.2
unnamed: DS1.3 (VO), RV1.2
unnamed: H1.MP, R1.1, R5.1
unnamed: H2.MP, R2.1, R6.1
unnamed: H3.MP, R3.1, R7.1
unnamed: H4.MP, R4.1, R8.1
unnamed: IC1.4, R10.2
unnamed: IC2.4, R16.2
unnamed: J2.4, R3.2, U1.30 (PD0)
unnamed: J2.5, R2.2, U1.31 (PD1)
unnamed: C13.2, J2.6
unnamed: P1.2 (PM), P2.1, P3.2 (PM), TR1.1
unnamed: F1.1, P2.2 (PM)
unnamed: R21.1, RV1.3
unnamed: R5.2, U1.19 (ADC6)
unnamed: R6.2, U1.22 (ADC7)
unnamed: C10.1, R19.2, U1.20 (AREF)
unnamed: R7.2, U1.23 (PC0)
unnamed: R8.2, U1.24 (PC1)
unnamed: U1.26 (PC3), U3.2 (Vout)
unnamed: R4.2, U1.28 (PC5)
unnamed: U1.32 (PD2), U2.2 (VOUT)
unnamed: R1.2, U1.1 (PD3)
unnamed: R14.2, U1.2 (PD4)
unnamed: R15.2, U1.9 (PD5)
unnamed: R9.1, U1.10 (PD6)
unnamed: C12.1, U1.7 (XTAL1/PB6), Y1.2
unnamed: C11.1, U1.8 (XTAL2/PB7), Y1.1

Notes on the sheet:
! *************** ATTENZIONE ************** ! A CAUSA DEI RISCHI CONNESSI ALLA SALUTE NON ALIMENTARE IL CIRCUITO A TENSIONI SUPERIORI A 48V ac! Questo circuito è di esempio al solo scopo di miglioramento del firmware. Non si assumono responsabilità in sede civile e/o penale relativi all'utilizzo in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

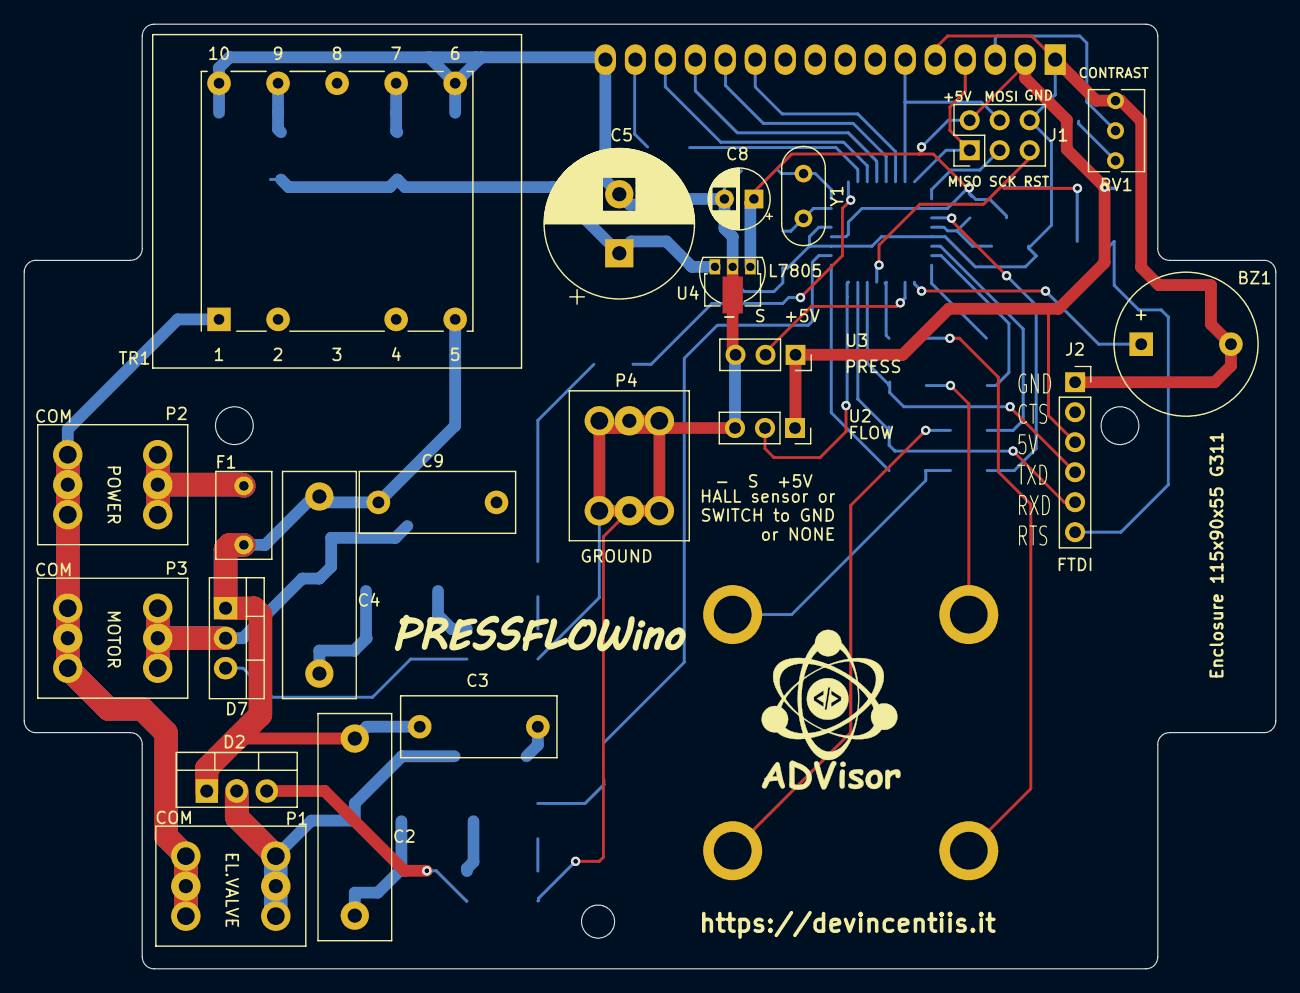
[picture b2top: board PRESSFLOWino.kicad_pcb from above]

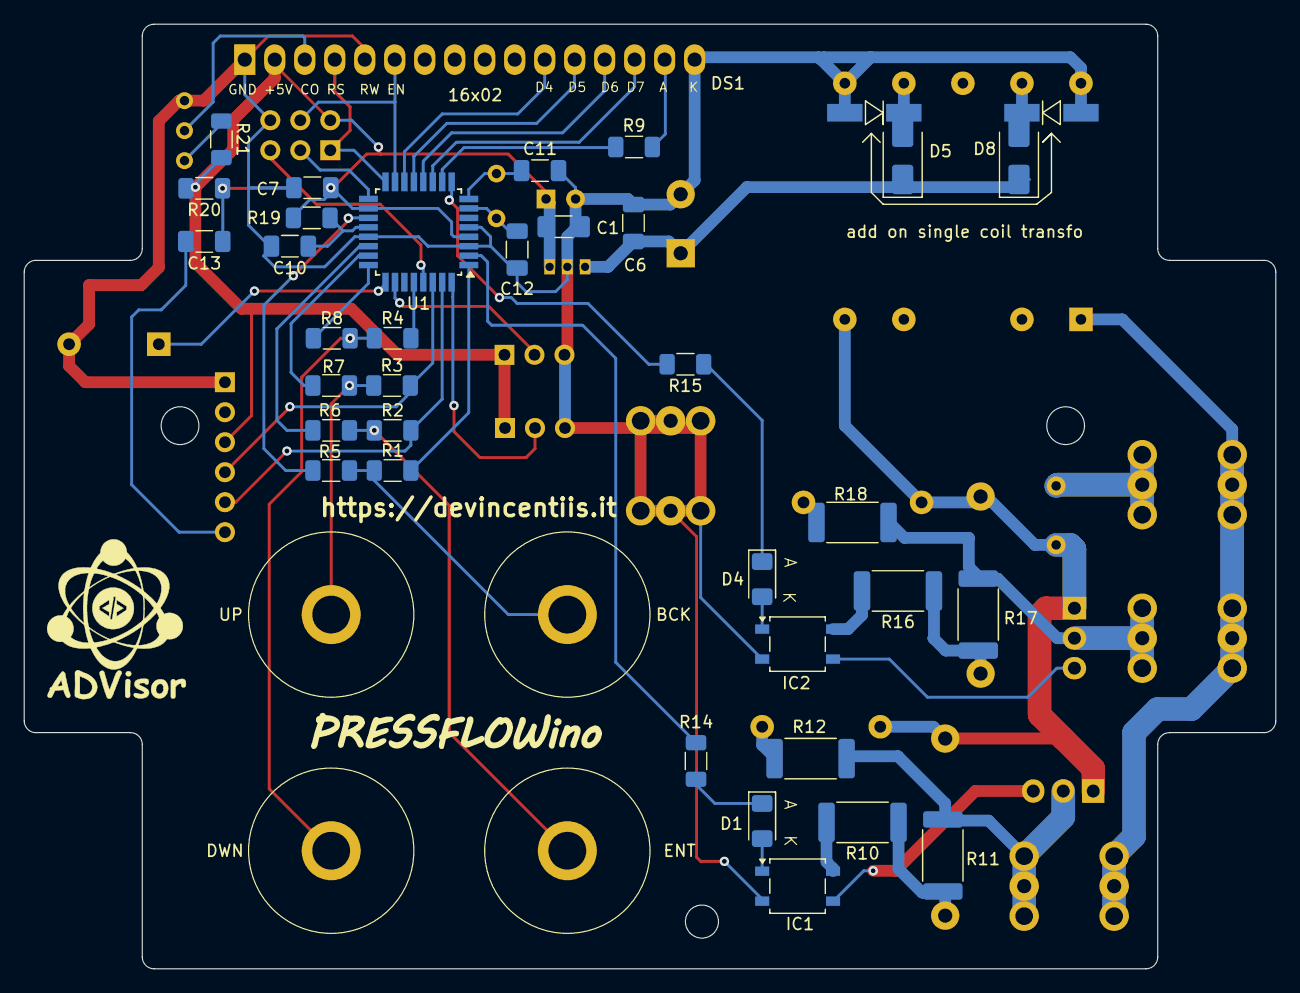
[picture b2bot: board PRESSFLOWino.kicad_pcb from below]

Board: 2 copper layers, 106.0 x 80.0 mm, 61 parts (39 on the bottom side), 55 nets.

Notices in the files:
AntonioDeVincentiis_classicESRmeter/README.md:
📝 License / Licenza:
Questo progetto è rilasciato sotto licenza MIT - consulta il file [LICENSE](LICENSE) per ulteriori dettagli.
This project is licensed under the MIT License - see the [LICENSE](LICENSE) file for details.
